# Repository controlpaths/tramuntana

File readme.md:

# Tramuntana — hardware hacking tool for embedded systems

An open bench tool for analysing and debugging embedded systems, built on
the RP2350 (Raspberry Pi Pico 2) and Zephyr OS. One USB cable, three serial
ports, one 16-pin header:

- **SPI master and sniffer** — SPIDriver-style `sel/write/read/unsel`
  transactions up to 75 MHz; passive full-duplex (MOSI + MISO) bus tap.
- **I2C master and sniffer** — I2CDriver-style `start/write/read/stop`
  primitives, scan, register access, bus recovery; passive decoder.
- **Oscilloscope** — 2 × 12-bit channels, 500 kS/s, pre-trigger.
- **Waveform generator** — sine/tri/saw/square/stairs/DC/arbitrary, 1 Hz–100 kHz.
- **Logic analyzer** — 8 channels, 150 MS/s, edge triggers in hardware,
  pattern trigger with pre-trigger, VCD export for PulseView.
- **USB-UART bridge** — the target's console as `/dev/ttyACM2`, baud rate
  follows whatever you open it with; RTS/DTR can drive the target's reset
  and boot pins, so esptool and friends flash through it.
- **Emulated I2C/SPI device** — the board answers on the target's bus from
  a register file the host loads and reads back.
- **Sequencer** — host-built step lists (GPIO, waits, bus transfers,
  captures) run on the board with microsecond timing.
- **Timeline** — the target's UART, sniffed buses, DIO edges and emulator
  transfers timestamped on one clock (host library, CLI, AI tools).
- Switched, protected 3.3 V rail for the target, switchable I2C pull-ups,
  RGB status LED and a TFT dashboard.

The passive instruments (sniffers, logic analyzer) only listen, so they can
watch a bus while the board's own master, the UART bridge or a target
drives it.

Two boards share the design: `tramuntana_r1a` (RP2350 on the PCB) and
`tramuntana_lite_r1a` (a Pico 2 soldered onto a two-layer carrier — the one
handed out at workshops). Firmware and host software are common.

## Documentation

The full documentation is in [`docs/`](docs/README.md): getting started,
a usage guide for every instrument, and complete references for the
Python library, the CLI, the shell, the binary protocol, the firmware
internals, the webapp and the AI tools.

## What's new

### Firmware 1.3.0, host package 2.3.0

Fixes found using the Tramuntana as the test bench of an FPGA module
library.

**Firmware**

- SPI emulator: written bytes go into the response table as they arrive,
  and the CS-rise interrupt rearms the shifters first. From CS rise to
  ready now takes under 2 µs; before, it took up to 160 µs after a
  write, and the next transaction was lost or garbled. A window that
  still starts too early is counted (`late`) and its event flagged
  `suspect`.
- I2C emulator: the START and STOP flags are read in one go. A STOP and
  the next START landing between two separate reads made the emulator
  NAK its own address after a write.
- I2C emulator: SDA is held ~330 ns after SCL falls (UM10204); it was
  30–140 ns.
- I2C sniffer: SCL must still be high a moment later before an SDA
  change counts as a START/STOP, so a slave with a short SDA hold no
  longer produces spurious STARTs or STOPs.
- Emulator events: the queue grows from 16 to 64, dropped events are
  counted and the next one is flagged (`gap`), reads log what went out
  on the bus, and display refreshes are rate-limited.
- Protocol: `EMU_STATUS` gains `dropped` and `late`; `EVT_EMU` flags
  bit 4 = suspect, bit 5 = gap.
- Sequencer: `PWM` (0x16) and `PWM_SYNC` (0x17) ops.

**Host**

- MCP server: `pwm_set` / `pwm_phase` / `pwm_sync` / `pwm_stop` /
  `pwm_status` tools, `pwm` ops in `sequence_run`, `spi_release` and
  `spi_transaction(release=)`, `names` as `{dio: name}`, and
  `logic_capture` waits up to 1 h (re-arming every 60 s).
- Library and CLI: `Spi.release()`, `tramuntana spi release`,
  `Sequence.pwm()` / `pwm_sync()`.
- Decoders: `sck_hz` / `scl_hz` are the median clock, and the new
  `bit_rate_hz` gives the average including pauses.
- `EmuTransfer.suspect` / `gap` and `Emu.status()` `dropped` / `late`;
  the webapp shows them.

**Docs:** measured SPI emulator speed limits, SPI master timing,
releasing pins after use, best-effort emulator events; the AI skill is
updated.

## Repository

```
fw/apps/tramuntana_fw/   Zephyr firmware                                -> its README
fw/boards/               devicetree for the board
fw/imgs/                 display images + font, with their generators
fw/build.sh              build / flash wrapper (local paths in fw/.env)
host/python/             Python package: library, `tramuntana` CLI, MCP server
                         and skill for AI agents                         -> its README
host/webapp/             browser front-end (Web Serial, no install)     -> its README
hw/tramuntana_lite_r1a/  KiCad project, hardware notes, 3D-printed case
hw/tramuntana_r1a/       KiCad project of the full board
docs/                    documentation                           -> its README
```

## Quick start

1. Flash `zephyr.uf2` from the latest GitHub release (hold BOOTSEL while
   plugging the Pico 2 in, copy the file to the `RP2350` drive), or build it
   yourself — see below. Three ports appear: shell, API, UART bridge.
2. Talk to it:

```bash
picocom /dev/ttyACM0           # the shell: try 'help', 'i2c scan', 'scope 1024'
source host/python/env.sh      # `tramuntana` command for this shell (creates the venv once)
tramuntana info
tramuntana i2c scan
tramuntana scope -n 2048 --trigger rising --level 1.65 --plot
tramuntana logic -n 65536 --rate 25M --vcd capture.vcd
picocom -b 115200 /dev/ttyACM2 # the target's UART, through the bridge
```

or open `host/webapp/index.html` in Chrome/Edge and press **Connect**.

3. Or hand it to an AI agent. The package carries an MCP server and the
   `tramuntana-debug` skill; one command registers both:

```bash
python3 -m venv ~/.venvs/tramuntana
~/.venvs/tramuntana/bin/pip install "./host/python[mcp]"
~/.venvs/tramuntana/bin/tramuntana ai install claude     # or opencode, copilot, all
# --project PATH registers it for that project only; 'ai uninstall' undoes it
```

Then ask: *"Power the target, scan the I2C bus and tell me what the devices
are."* See [AI tools](docs/19-ai-tools.md).

## `tramuntana` command reference

`source host/python/env.sh` defines the command in the current shell (it
runs `host/python/.venv/bin/tramuntana`, creating the venv the first time).
It talks to the board's API port, found automatically by USB id.

Conventions: bytes and I2C addresses are **hex** (`9f 00 ff`, `9f00ff`,
`68`); frequencies accept `k`/`M` suffixes (`400k`, `8M`, `1e6`); volts are
decimal (`1.65`). Exit code 0 on success, 1 if no board is found, 2 if the
board rejected the command (NAK, busy, bad argument…), 3 on a link error.

### Global options

| Option | Meaning |
|---|---|
| `--port /dev/ttyACMx` | use this API port instead of autodetecting |
| `--serial <id>` | pick the board with this USB serial number (several boards plugged in) |

### Board

| Command | What it does |
|---|---|
| `tramuntana list` | list connected boards and their shell / API / UART ports |
| `tramuntana info` | firmware version, board, system clock, chip id, protocol version, port |
| `tramuntana status` | who owns each DIO pin, power, pull-ups, state of every instrument, API bytes dropped |
| `tramuntana power [on\|off]` | switch the target's 3.3 V rail (J1.1); no argument prints its state |
| `tramuntana pullups [on\|off]` | I2C pull-up bias on DIO6/DIO7; no argument prints its state |
| `tramuntana led <colour>` | `off red green blue yellow cyan magenta white`, or `auto` to give it back to the firmware |
| `tramuntana adc [0\|1]` | one reading of AIN0/AIN1 in volts (default AIN0) |
| `tramuntana display <text…>` | show up to 24 characters on the board's screen |
| `tramuntana pinout [off] [--seconds N\|--hold]` | draw J1 (every pin's name and function) in the terminal and on the board's screen, 60 s by default; works without a board (terminal only) |
| `tramuntana dio read` | levels of DIO7..DIO0 |
| `tramuntana dio dir <mask> <out_mask>` | set direction of the pins in `mask` (bit i = DIOi, 1 = output) |
| `tramuntana dio write <mask> <value>` | drive the output pins in `mask` (set them as outputs first) |
| `tramuntana bootloader` | reboot into the UF2 bootloader (the `RP2350` drive appears) |

`dio` masks accept `0x..`, `0b..` or decimal (`0x0f`, `0b1010`, `15`).

### SPI — DIO2 CS, DIO3 MISO, DIO4 MOSI, DIO5 SCK

| Command | What it does |
|---|---|
| `tramuntana spi conf <freq> [mode] [--lsb]` | clock (up to 75 MHz), mode 0–3 (default 0), LSB first; prints the actual clock |
| `tramuntana spi sel` | CS low |
| `tramuntana spi unsel` | CS high |
| `tramuntana spi release` | stop driving DIO2..5 (the master leaves CS, SCK and MOSI driven after each command) |
| `tramuntana spi write <bytes…>` | send bytes, CS untouched |
| `tramuntana spi read <n>` | read n bytes (sends 0x00), CS untouched |
| `tramuntana spi xfer <bytes…>` | full duplex: send bytes, print what came back, CS untouched |
| `tramuntana spi txn [bytes…] [--read N]` | whole transaction: CS low, write bytes, read N, CS high |
| `tramuntana spi sniff [--mode M]` | passive tap of MOSI and MISO, one line per CS-low message, until Ctrl-C (mode defaults to the one set with `conf`) |

```bash
tramuntana spi conf 8M 0
tramuntana spi txn 9f --read 3                  # JEDEC id of a SPI flash
tramuntana spi txn 03 00 00 00 --read 256       # first page of the flash
tramuntana spi sel && tramuntana spi write 06 && tramuntana spi unsel   # write enable, step by step
```

### I2C — DIO6 SCL, DIO7 SDA

| Command | What it does |
|---|---|
| `tramuntana i2c conf <freq> [--no-pullups]` | bus clock (1 kHz–1 MHz); turns the board's pull-ups on unless `--no-pullups` |
| `tramuntana i2c scan` | probe 0x08–0x77 and print the address map |
| `tramuntana i2c read <addr>` | read 1 byte from a device |
| `tramuntana i2c read <addr> <reg> [n]` | register read: write `reg`, repeated START, read n bytes (default 1). `reg` takes 2 hex digits per byte, so `0010` is a 16-bit address (24LC32 and up, VL53L1X…) |
| `tramuntana i2c write <addr> <bytes…>` | START, address, bytes, STOP; prints how many bytes were ACKed |
| `tramuntana i2c regs <addr>` | dump registers 0x00–0xff (16 at a time; blocks that NAK show as `ff`) |
| `tramuntana i2c sniff [--pullups]` | passive decoder, one line per START…STOP (`S 68W+ 75+  S 68R+ 71- P`), until Ctrl-C |
| `tramuntana i2c reset` | bus recovery: up to 9 SCL pulses and a STOP to free a stuck slave |

```bash
tramuntana i2c conf 400k
tramuntana i2c scan
tramuntana i2c read 68 75              # WHO_AM_I of an MPU-6050
tramuntana i2c write 68 6b 00          # wake it up
tramuntana i2c regs 50                 # dump an EEPROM's first 256 bytes
```

The low-level primitives (`start`, raw write/read, `stop`) are in the shell,
the Python library and the webapp; the CLI covers complete transactions.

### Oscilloscope — AIN0 (and AIN1)

`tramuntana scope [options]` captures, prints per-channel min / max / Vpp /
mean / RMS / frequency, and optionally saves or plots.

| Option | Default | Meaning |
|---|---|---|
| `-n N` | 2048 | samples per channel (16384 in total max) |
| `--ch 1\|2` | 1 | AIN0 only, or AIN0 + AIN1 |
| `--rate R` | 500k | sample rate per channel (500 kS/s total max, shared between channels) |
| `--trigger none\|rising\|falling` | none | edge on AIN0 |
| `--level V` | 1.65 | trigger level in volts |
| `--pre N` | 0 | samples kept before the trigger |
| `--csv file` | | save `t,ch0[,ch1]` in volts, t = 0 at the trigger |
| `--plot` | | show it with matplotlib (`host/python/.venv/bin/pip install matplotlib`) |

```bash
tramuntana scope -n 4096 --trigger rising --level 1.65 --pre 1024 --plot
tramuntana scope --ch 2 --rate 100k --csv two_channels.csv
```

### Waveform generator — AOUT0

| Command | What it does |
|---|---|
| `tramuntana awg sine <freq> [--amp V] [--offset V]` | sine; amplitude is the peak around the offset (defaults 1.0 V around 1.65 V) |
| `tramuntana awg tri <freq> [--amp V] [--offset V]` | triangle |
| `tramuntana awg saw <freq> [--amp V] [--offset V]` | sawtooth (rising ramp) |
| `tramuntana awg square <freq> [--amp V] [--offset V] [--param duty%]` | square, duty cycle in % (default 50) |
| `tramuntana awg stairs <freq> [--amp V] [--offset V] [--param steps]` | staircase with that many steps (default 8) |
| `tramuntana awg dc <volts>` | constant level |
| `tramuntana awg step <from_v> <to_v> <ms>` | hold `from_v`, then jump to `to_v` after `ms` |
| `tramuntana awg off` | stop, output low |
| `tramuntana awg status` | what is running |

Frequencies go from 1 Hz to 100 kHz; the command prints the frequency
actually achieved. Arbitrary waveforms are loaded from the Python library
(`t.awg.arbitrary(...)`) or the webapp.

### PWM outputs — any DIO

| Command | What it does |
|---|---|
| `tramuntana pwm set <dio> <freq> <duty%> [--invert]` | PWM on a DIO; pairs 7/6, 5/4, 3/2, 1/0 share a frequency |
| `tramuntana pwm phase <dio> <deg>` / `pwm sync [mask]` | phase per pair, restart the pairs together |
| `tramuntana pwm stop <dio\|all>` / `pwm status` | stop / show every output |

### Logic analyzer — DIO0..DIO7

`tramuntana logic [options]` captures, prints the number of transitions per
channel, and optionally saves or plots.

| Option | Default | Meaning |
|---|---|---|
| `-n N` | 16384 | samples (131072 max, 122880 with a pattern trigger) |
| `--rate R` | 150M | sample rate (150 MS/s max; 15 MS/s max with a pattern trigger) |
| `--trigger none\|rising\|falling\|pattern` | none | edge on one pin, or a pattern on several |
| `--pin P` | 0 | DIO used by `rising`/`falling` |
| `--mask M` / `--value V` | 0 / 0 | pattern trigger: fires when `(sample & mask) == value` (bit i = DIOi) |
| `--pre N` | 0 | samples kept before the trigger (pattern trigger only) |
| `--timeout ms` | 5000 | give up if the trigger doesn't come |
| `--vcd file` | | save for PulseView / GTKWave |
| `--csv file` | | save `t,DIO0..DIO7`, t = 0 at the trigger |
| `--plot` | | show the 8 lanes with matplotlib |

```bash
tramuntana logic -n 131072 --rate 150M --trigger rising --pin 5 --vcd spi.vcd
tramuntana logic -n 100000 --rate 10M --trigger pattern --mask 0x80 --value 0 --pre 2000 --vcd i2c.vcd   # I2C START (SDA low)
```

### UART bridge — DIO1 TX, DIO0 RX

| Command | What it does |
|---|---|
| `tramuntana uart` / `tramuntana uart status` | bridge active or not, baud rate, bytes received / sent, and which port to open |
| `tramuntana uart auto` | (default) bridge on while a program has the bridge port open |
| `tramuntana uart on [--baud B]` | force it on; `--baud` overrides the rate the host sets on the port |
| `tramuntana uart off` | force it off, DIO0/DIO1 free for plain GPIO |

The data itself goes through the third serial port, e.g.
`picocom -b 115200 /dev/ttyACM2` (the baud rate you open it with is the one
used on the target, unless overridden with `--baud`).

| Command | What it does |
|---|---|
| `tramuntana uart ctrl esp --reset R --boot B` | RTS/DTR of the bridge port drive DIO R / DIO B (open-drain) with the ESP32/ESP8266 auto-reset logic: `esptool --port /dev/ttyACM2 ...` resets the target into its ROM loader by itself |
| `tramuntana uart ctrl direct --reset R --boot B` | reset follows RTS, boot follows DTR (an adapter wired straight to the pins) |
| `tramuntana uart ctrl off` | release them |

### Emulated device, timeline, DIO watch

| Command | What it does |
|---|---|
| `tramuntana emu i2c ADDR [--scl D --sda D] [--pullups] [--set REG=HEX..]` | answer as an I2C device at ADDR (default on DIO6/DIO7), registers loaded first |
| `tramuntana emu spi [--mode M] [--cs --sck --mosi --miso D] [--set REG=HEX..]` | answer as a SPI device (bit 7 of the command byte = read) |
| `tramuntana emu set REG HEX..` / `emu regs [REG] [N]` | load / dump registers |
| `tramuntana emu status` / `emu log` / `emu off` | counters / live transfers / stop |
| `tramuntana watch MASK` | timestamped edges on the DIOs in MASK, until Ctrl-C |
| `tramuntana timeline [--watch MASK] [--uart BAUD] [--i2c] [--spi MODE]` | live timeline: the target's UART lines, sniffed messages, DIO edges and emulator transfers on one clock |

The sequencer has no CLI front: build a `Sequence` in Python
([API](host/python/API.md#tseq--sequencer)) or use the AI tools'
`sequence_run`.

## Building the firmware

A Zephyr workspace (per the
[getting started guide](https://docs.zephyrproject.org/latest/develop/getting_started/index.html))
and the Zephyr SDK, plus `device-tree-compiler` on the host. `fw/` is not
its own west workspace; `build.sh` builds an app against that install.
Tell it where they are in `fw/.env` (defaults: `~/zephyrproject` and
`~/zephyr-sdk-1.0.1`):

```bash
cd fw
cp .env.example .env             # then edit ZEPHYRPROJECT / ZEPHYR_SDK
./build.sh                       # builds tramuntana_fw
./build.sh flash                 # build + flash (reboots the board into the
                                 # UF2 bootloader over USB, no BOOTSEL needed)
```

Only the first flash — or recovering from a hung firmware — needs BOOTSEL
held while plugging the board in.

## Header

```
 1 3V3 (switched)   2 GND       3 AIN0     4 GND      5 AIN1    6 GND
 7 AOUT0            8 VREF      9 DIO0    10 DIO1    11 DIO2   12 DIO3
13 DIO4            14 DIO5     15 DIO6    16 DIO7

DIO0/1 = UART RX/TX    DIO2..5 = SPI CS / MISO / MOSI / SCK    DIO6/7 = I2C SCL/SDA
DIO0..7 = GPIO and logic analyzer channels 0..7   (`tramuntana pinout` draws it)
```

## License

| Part | License |
|---|---|
| Firmware (`fw/`), host software (`host/`: library, CLI, MCP server, webapp) | [MIT](LICENSES/MIT.txt) |
| Hardware (`hw/`: schematics, PCB, fabrication files, case) | [CERN-OHL-P-2.0](LICENSES/CERN-OHL-P-2.0.txt) |
| Documentation (`docs/`, READMEs, images) | [CC-BY-4.0](LICENSES/CC-BY-4.0.txt) |

See [LICENSE](LICENSE).

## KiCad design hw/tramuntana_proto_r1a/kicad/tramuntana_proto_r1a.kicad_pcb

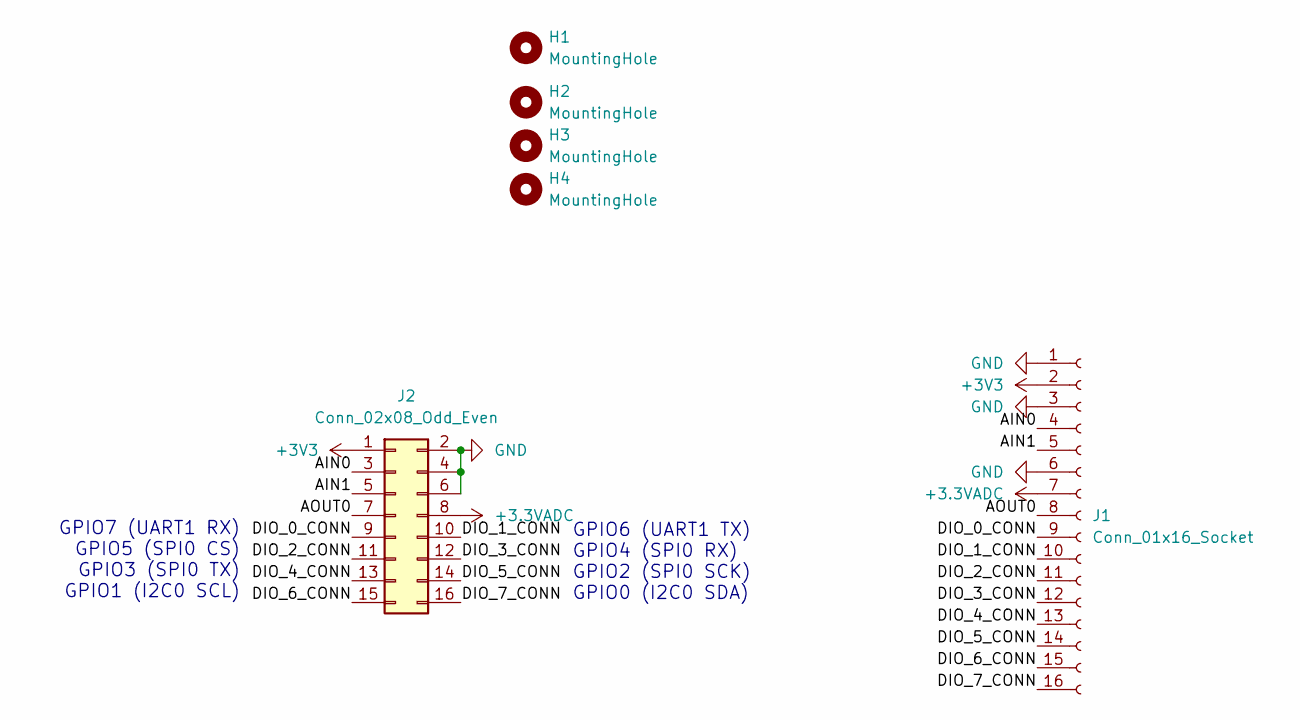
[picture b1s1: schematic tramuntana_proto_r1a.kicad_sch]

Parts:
H1, H2, H3, H4: MountingHole; MountingHole_3.2mm_M3
J1: Conn_01x16_Socket; PinSocket_1x16_P2.54mm_Vertical
J2: Conn_02x08_Odd_Even; PinSocket_2x08_P2.54mm_Horizontal

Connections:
+3.3VADC: J1.7, J2.8
+3V3: J1.2, J2.1
/AIN0: J1.4, J2.3
/AIN1: J1.5, J2.5
/AOUT0: J1.8, J2.7
/DIO_0_CONN: J1.9, J2.9
/DIO_1_CONN: J1.10, J2.10
/DIO_2_CONN: J1.11, J2.11
/DIO_3_CONN: J1.12, J2.12
/DIO_4_CONN: J1.13, J2.13
/DIO_5_CONN: J1.14, J2.14
/DIO_6_CONN: J1.15, J2.15
/DIO_7_CONN: J1.16, J2.16
GND: J1.1, J1.3, J1.6, J2.2, J2.4, J2.6

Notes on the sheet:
GPIO7 (UART1 RX) GPIO5 (SPI0 CS) GPIO3 (SPI0 TX) GPIO1 (I2C0 SCL)
GPIO6 (UART1 TX) GPIO4 (SPI0 RX) GPIO2 (SPI0 SCK) GPIO0 (I2C0 SDA)

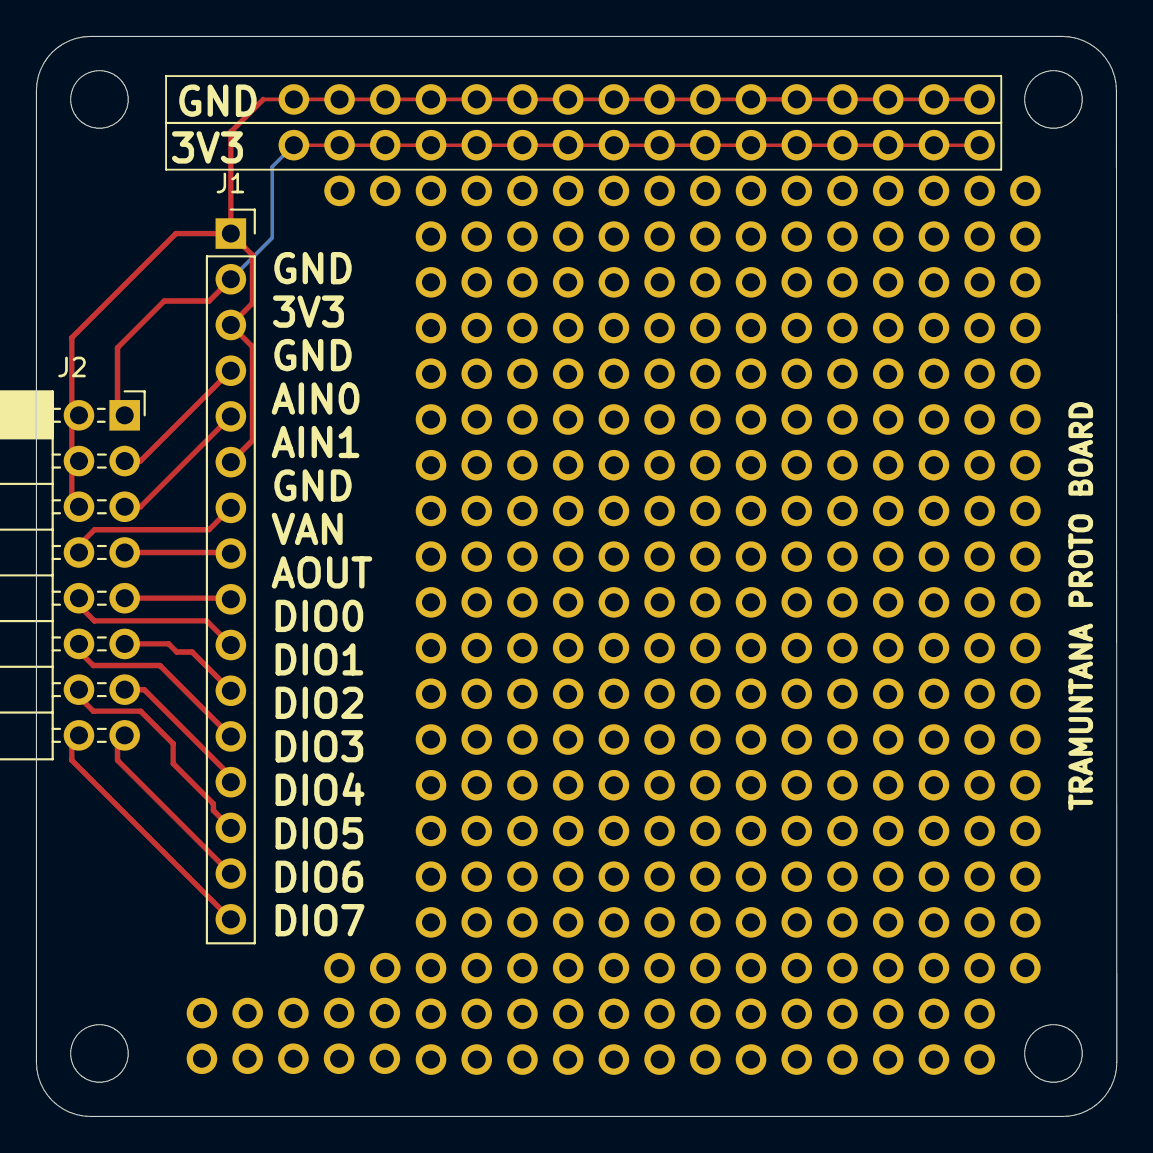
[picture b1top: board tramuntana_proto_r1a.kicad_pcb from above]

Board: 2 copper layers, 60.0 x 60.0 mm, 6 parts (0 on the bottom side), 14 nets.

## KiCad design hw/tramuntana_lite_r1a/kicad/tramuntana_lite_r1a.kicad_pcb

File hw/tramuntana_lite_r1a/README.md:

# Tramuntana Lite r1a

RP2350-based board. The KiCad project lives in [kicad/](kicad/). Firmware
for this board lives in the workspace-wide [../../fw/](../../fw/) tree (see
its README for building/flashing) — bring-up is happening on a
**Raspberry Pi Pico 2** (RP2350) ahead of the final board, since the MCU
(A1 in the schematic) is a Pico module soldered straight onto this board.

---

## Board devicetree

There's no dedicated Zephyr board port for tramuntana_lite_r1a (that's more
machinery than a bring-up needs). Instead, the hardware is described in
[../../fw/boards/tramuntana_lite_r1a-common.dtsi](../../fw/boards/tramuntana_lite_r1a-common.dtsi) —
an app-level devicetree overlay applied on top of the stock
`rpi_pico2/rp2350a/m33` board, shared by every app under `fw/apps/`.

### What's on the board

Derived from the schematic netlist ([kicad/tramuntana_lite_r1a.kicad_sch](kicad/tramuntana_lite_r1a.kicad_sch),
cross-checked against `kicad-cli sch export netlist`):

| Header pin | Net | Pico GPIO | Devicetree |
|---|---|---|---|
| J1.1 | `/3V3_TARGET` (switched, via Q1) | GPIO11 (enable, active-low) | `regulator-fixed`, alias `targetpwr` |
| J1.3 | `/AIN0` | GPIO26 / ADC0 | `&adc`, channel 0 |
| J1.5 | `/AIN1` | GPIO27 / ADC1 | `&adc`, channel 1 |
| J1.7 | `/AOUT0` | GPIO8 | `zephyr,user` / `aout0-gpios` |
| J1.9-16 | `DIO0`..`DIO7` | GPIO7..GPIO0 | `zephyr,user` / `dio-gpios` |
| — | `/DIO_PU_ENABLE` (shared pull-up bias for DIO6/DIO7) | GPIO10 | `zephyr,user` / `dio-pu-enable-gpios` |
| J1.11-14 (DIO2-5) | SPI0 CSN/RX/TX/SCK | GPIO5/4/3/2 | `&spi0` (hardware CS on DIO2) |
| J1.15-16 (DIO6/7) | I2C0 SCL/SDA | GPIO1/0 | `&i2c0` (100kHz by default) |
| J2.3/4 | SPI1 SCK/MOSI | GPIO14/15 | `&spi1` (hardware CS on GPIO13) |
| J2.5/6/7 | TFT reset/DC/CS | GPIO16/17/13 | the `zephyr,mipi-dbi-spi` + `sitronix,st7735r` nodes |
| D3 (RGB LED) | `/LEDR`, `/LEDG`, `/LEDB` | GPIO20/21/22 | `gpio-leds` (active-low), aliases `led-r`/`led-g`/`led-b` |

Q1 is a P-FET high-side switch (R17 pulls its gate to +3V3 at reset, so the
rail is off by default); D3 is a common-anode RGB LED, so all three legs
sink current through their GPIO and are active-low. D7 (power-good LED) and
the protection parts (F1 fuse, D1/D2 clamps, the series resistors) aren't
modeled — they're not GPIO-controlled, just electrical protection and
indication.

Confirmed on real hardware: D3's red and green legs are swapped relative to
the schematic's own net names (`LEDR`/`LEDG`) — GPIO20 is actually green and
GPIO21 is actually red, the opposite of what the net names say. The
devicetree's `led-r`/`led-g` aliases are wired to match reality (GPIO21/
GPIO20), not the schematic labels, so software colors are correct even
though the underlying net names are misleading.

One thing worth knowing: UART0 (GPIO0/GPIO1) is this board target's default
Zephyr console, and that's DIO7/DIO6 on the target header here — the same
two pins `&i2c0` uses. The firmware (`tramuntana_fw`) overrides the
console to run over the Pico's own USB port (CDC-ACM) instead, precisely to
keep those two header pins free for I2C. Any other app built for this board
that doesn't override it still uses UART0 for its boot log — keep J1's DIO6/DIO7
unplugged while flashing/testing those, and don't expect I2C0 to work in
them at the same time as the console.

`&spi0` and `&i2c0` are enabled alongside `dio-gpios`'s plain-GPIO view of
the same pins (DIO2-7): nothing stops an app from referencing both, but the
RP2350 only drives one function per pin at a time, so pick whichever one an
app actually needs for DIO2-7 rather than mixing them on the same pins.

The display node assumes a generic 1.8" 128x160 ST7735R module (GND, 3V3,
SCK, MOSI, RST, DC, CS, BL on J2, in that order; BL is tied straight to
+3V3, no GPIO control). If the picture comes out shifted or mirrored, that's
the well-known ST7735 clone quirk where `x-offset`/`y-offset`/`madctl` differ
by tab color — adjust them in `tramuntana_lite_r1a-common.dtsi`.

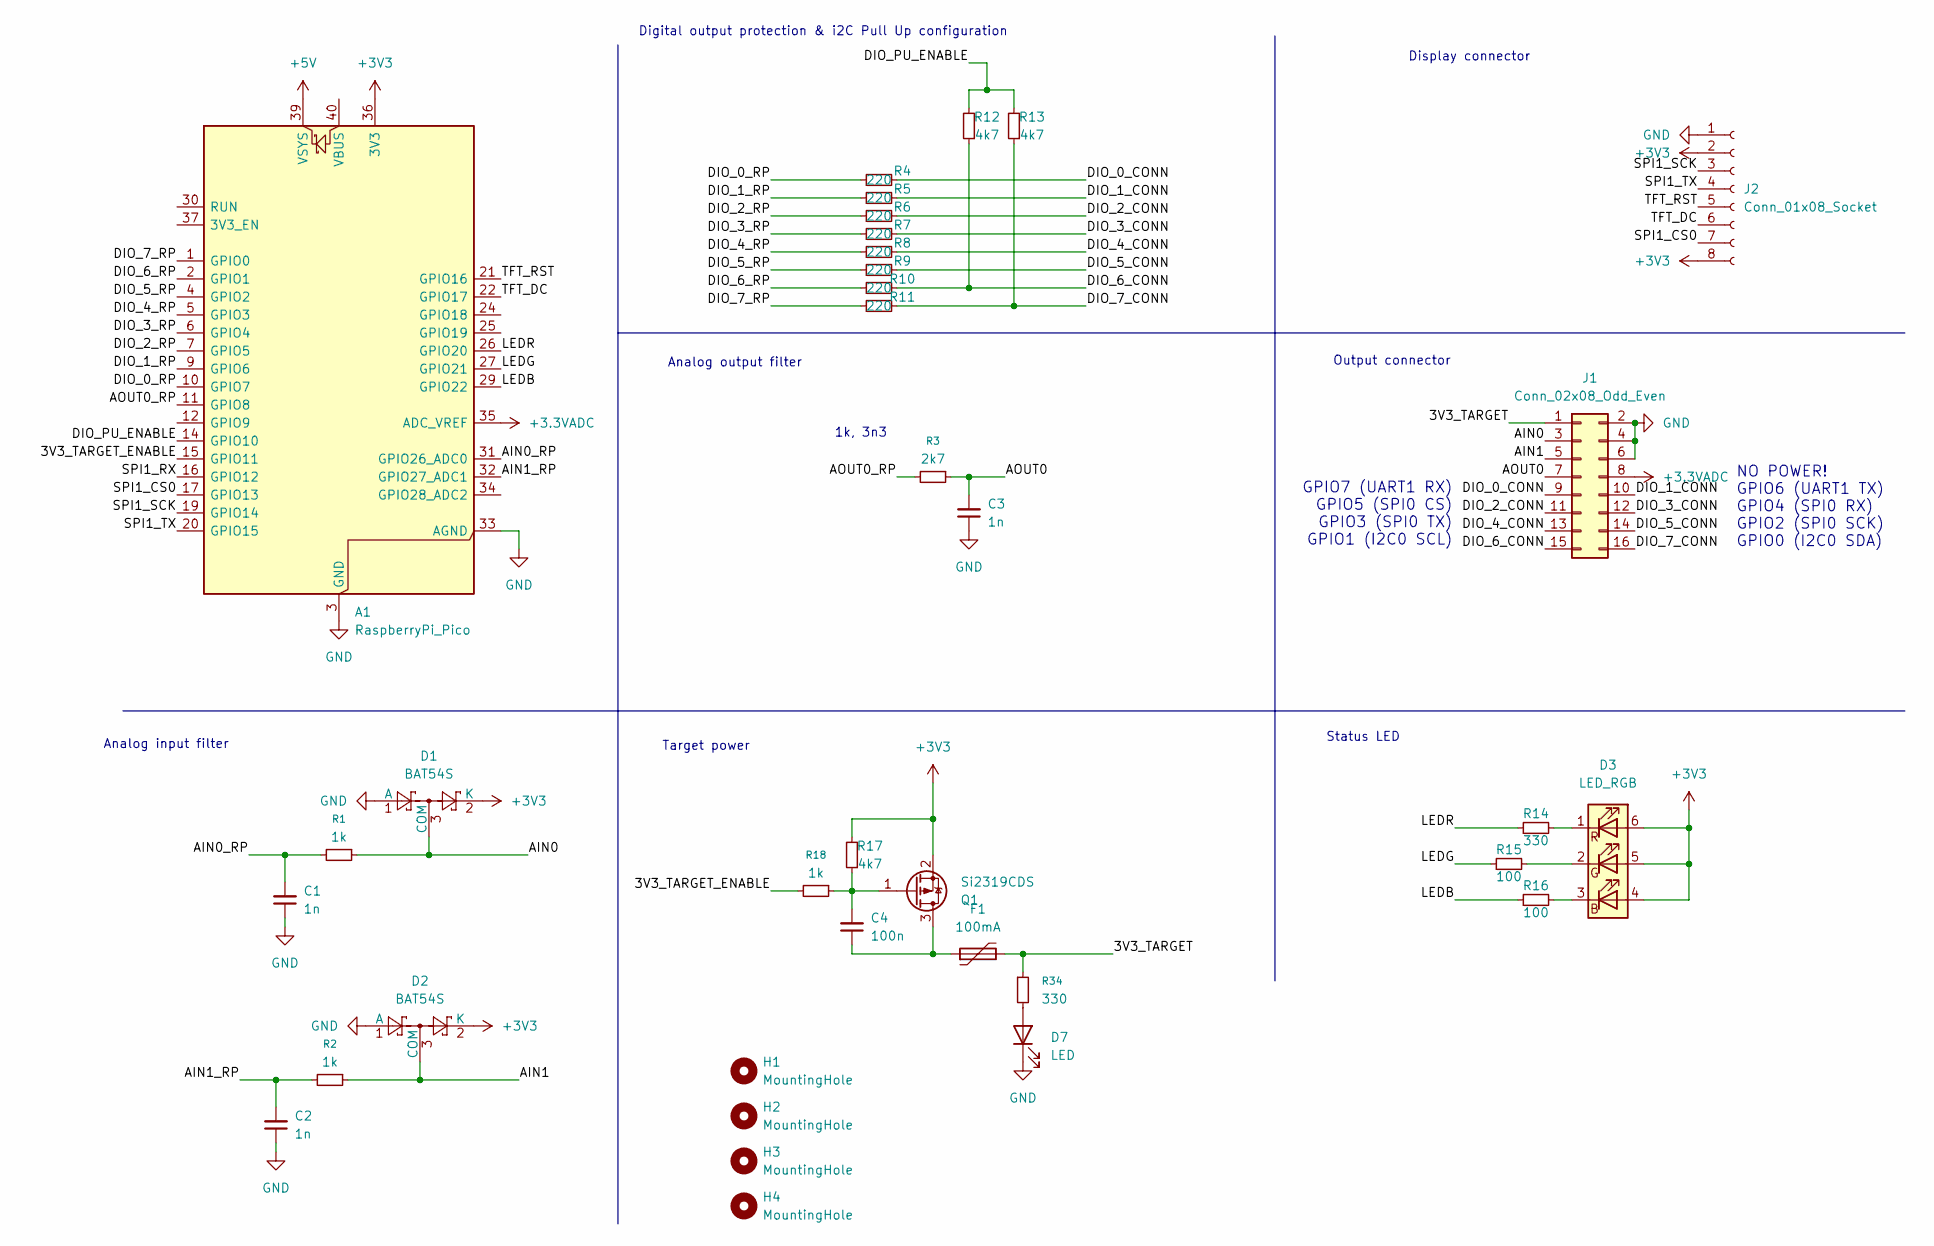
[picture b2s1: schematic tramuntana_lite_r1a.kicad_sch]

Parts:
A1: RaspberryPi_Pico; RaspberryPi_Pico_Common_Unspecified
C1, C2, C3: 1n; C_0603_1608Metric_Pad1.08x0.95mm_HandSolder
C4: 100n; C_0603_1608Metric_Pad1.08x0.95mm_HandSolder
D1, D2: BAT54S; SOT-23
D3: LED_RGB; LED_RGB_5050-6
D7: LED; LED_0603_1608Metric
F1: 100mA; Fuse_0805_2012Metric
H1, H2, H3, H4: MountingHole; MountingHole_3.2mm_M3
J1: Conn_02x08_Odd_Even; PinHeader_2x08_P2.54mm_Horizontal
J2: Conn_01x08_Socket; PinHeader_1x08_P2.54mm_Vertical
Q1: Si2319CDS; SOT-23
R1, R2: 1k; R_0603_1608Metric_Pad0.98x0.95mm_HandSolder
R3: 2k7; R_0603_1608Metric_Pad0.98x0.95mm_HandSolder
R4, R5, R6, R7, R8, R9, R10, R11: 220; R_0603_1608Metric
R12, R13, R17: 4k7; R_0603_1608Metric
R14: 330; R_0603_1608Metric
R15, R16: 100; R_0603_1608Metric
R18: 1k; R_0603_1608Metric
R34: 330; R_0603_1608Metric_Pad0.98x0.95mm_HandSolder

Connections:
+3.3VADC: A1.35 (ADC_VREF), J1.8
+3V3: A1.36 (3V3), D1.2 (K), D2.2 (K), D3.4 (BA), D3.5 (GA), D3.6 (RA), J2.2, J2.8, Q1.2 (S), R17.2
+5V: A1.39 (VSYS)
/3V3_TARGET: F1.2, J1.1, R34.1
/3V3_TARGET_ENABLE: A1.15 (GPIO11), R18.2
/AIN0: D1.3 (COM), J1.3, R1.1
/AIN0_RP: A1.31 (GPIO26_ADC0), C1.2, R1.2
/AIN1: D2.3 (COM), J1.5, R2.1
/AIN1_RP: A1.32 (GPIO27_ADC1), C2.2, R2.2
/AOUT0: C3.2, J1.7, R3.1
/AOUT0_RP: A1.11 (GPIO8), R3.2
/DIO_0_CONN: J1.9, R4.2
/DIO_0_RP: A1.10 (GPIO7), R4.1
/DIO_1_CONN: J1.10, R5.2
/DIO_1_RP: A1.9 (GPIO6), R5.1
/DIO_2_CONN: J1.11, R6.2
/DIO_2_RP: A1.7 (GPIO5), R6.1
/DIO_3_CONN: J1.12, R7.2
/DIO_3_RP: A1.6 (GPIO4), R7.1
/DIO_4_CONN: J1.13, R8.2
/DIO_4_RP: A1.5 (GPIO3), R8.1
/DIO_5_CONN: J1.14, R9.2
/DIO_5_RP: A1.4 (GPIO2), R9.1
/DIO_6_CONN: J1.15, R10.2, R12.1
/DIO_6_RP: A1.2 (GPIO1), R10.1
/DIO_7_CONN: J1.16, R11.2, R13.1
/DIO_7_RP: A1.1 (GPIO0), R11.1
/DIO_PU_ENABLE: A1.14 (GPIO10), R12.2, R13.2
/LEDB: A1.29 (GPIO22), R16.1
/LEDG: A1.27 (GPIO21), R15.1
/LEDR: A1.26 (GPIO20), R14.1
/SPI1_CS0: A1.17 (GPIO13), J2.7
/SPI1_RX: A1.16 (GPIO12)
/SPI1_SCK: A1.19 (GPIO14), J2.3
/SPI1_TX: A1.20 (GPIO15), J2.4
/TFT_DC: A1.22 (GPIO17), J2.6
/TFT_RST: A1.21 (GPIO16), J2.5
GND: A1.3 (GND), A1.8 (GND), A1.13 (GND), A1.18 (GND), A1.23 (GND), A1.28 (GND), A1.33 (AGND), A1.38 (GND), C1.1, C2.1, C3.1, D1.1 (A), D2.1 (A), D7.1 (K), J1.2, J1.4, J1.6, J2.1
unnamed: D3.3 (BK), R16.2
unnamed: D3.2 (GK), R15.2
unnamed: D3.1 (RK), R14.2
unnamed: D7.2 (A), R34.2
unnamed: C4.1, F1.1, Q1.3 (D)
unnamed: C4.2, Q1.1 (G), R17.1, R18.1

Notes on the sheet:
Target power
Output connector
Analog output filter
Analog input filter
NO POWER! GPIO6 (UART1 TX) GPIO4 (SPI0 RX) GPIO2 (SPI0 SCK) GPIO0 (I2C0 SDA)
Display connector
Status LED
Digital output protection & i2C Pull Up configuration
1k, 3n3
GPIO7 (UART1 RX) GPIO5 (SPI0 CS) GPIO3 (SPI0 TX) GPIO1 (I2C0 SCL)

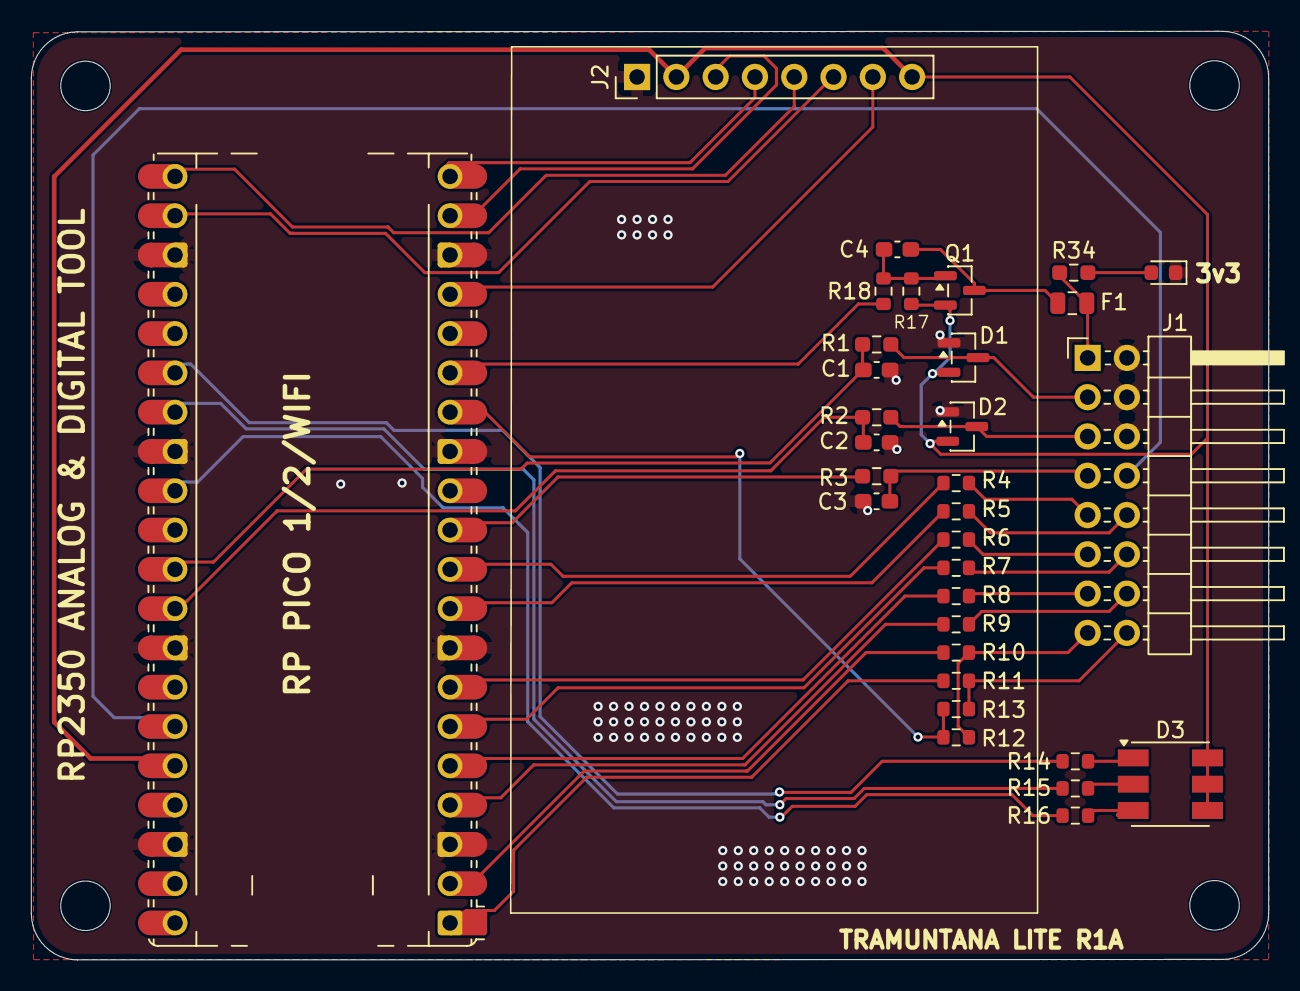
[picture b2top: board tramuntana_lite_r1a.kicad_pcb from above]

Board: 2 copper layers, 80.0 x 60.0 mm, 36 parts (0 on the bottom side), 42 nets.

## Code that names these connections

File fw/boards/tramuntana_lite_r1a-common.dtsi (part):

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 *
 *   Header pin | Net              | Pico GPIO | Devicetree
 *   -----------|------------------|-----------|---------------------------
 *   J1.1       | /3V3_TARGET      | GPIO11    | regulator-fixed, alias targetpwr
 *   J1.3       | /AIN0            | GPIO26    | &adc channel 0
 *   J1.5       | /AIN1            | GPIO27    | &adc channel 1
 *   J1.7       | /AOUT0           | GPIO8     | &pwm slice 4A (aout0_pwm_default)
 *   J1.9-16    | DIO0..DIO7       | GPIO7..0  | zephyr,user dio-gpios
 *   -          | /DIO_PU_ENABLE   | GPIO10    | zephyr,user dio-pu-enable-gpios
 *   J2.3/4     | SPI1 SCK/MOSI    | GPIO14/15 | &spi1
 *   J2.5/6/7   | TFT RST/DC/CS    | GPIO16/17/13 | mipi-dbi-spi + st7735r
 *   D3         | LEDR/LEDG/LEDB   | GPIO20/21/22 | gpio-leds, alias led-r/g/b
 *
 * DIO2..DIO5 (GPIO5..2) and DIO6/DIO7 (GPIO1/0) double as the RP2350's
 * native SPI0 and I2C0, since that's what the connector's 8 GPIOs are for:
 *
 *   DIO pin | Pico GPIO | SPI0 signal | I2C0 signal
 *   --------|-----------|-------------|------------
 *   DIO2    | GPIO5     | CSN         | -
 *   DIO3    | GPIO4     | RX (MISO)   | -
 *   DIO4    | GPIO3     | TX (MOSI)   | -
 *   DIO5    | GPIO2     | SCK         | -
 *   DIO6    | GPIO1     | -           | SCL
 *   DIO7    | GPIO0     | -           | SDA
 *
 * &spi0/&i2c0 below are enabled alongside dio-gpios's plain-GPIO view of
 * the same pins - nothing stops an app from using both nodes, but only one
 * function actually drives a given pin at a time, so pick one per DIO pin
 * in practice. DIO6/DIO7 (I2C0) also double as UART0 (GPIO0/1), Zephyr's
 * default console on this board target - see the note further down.
 * tramuntana_fw disables UART0 and runs its bridge on UART1 instead, at
 * DIO1 (GPIO6, TX) / DIO0 (GPIO7, RX) through the UART_AUX pin function.
 *
 * Series resistors, the target-rail fuse/clamp diodes and the power-good
 * LED (D7) are electrical protection/indication only - not modeled here.
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  };

  /* Q1 (P-FET high-side switch) gates the target's 3.3V rail. R17 pulls
   * the gate to 3V3 (off) at reset; GPIO11 low turns the rail on. */
  target_3v3_regulator: regulator-target-3v3 {
    compatible = "regulator-fixed";
    regulator-name = "target-3v3-regulator";
    enable-gpios = <&gpio0 11 GPIO_ACTIVE_LOW>;
    regulator-boot-off;
  };

  /* D3 is a common-anode RGB LED tied to +3V3: each leg sinks current
   * through the RP2350 GPIO, so all three lines are active-low.
   *
   * The schematic nets are named LEDR=GPIO20/LEDG=GPIO21/LEDB=GPIO22, but
   * on real hardware GPIO20 lights the green leg and GPIO21 the red one
   * (D3's symbol/footprint pinout doesn't match its net names) - swapped
   * here so led-r/led-g actually match what lights up. */
  leds {
    compatible = "gpio-leds";
    led_r: led-r {
      gpios = <&gpio0 21 GPIO_ACTIVE_LOW>;
    };
    led_g: led-g {
      gpios = <&gpio0 20 GPIO_ACTIVE_LOW>;
    };
    led_b: led-b {
      gpios = <&gpio0 22 GPIO_ACTIVE_LOW>;
    };
  };

  /* J1's 8 general-purpose header pins, exposed as plain GPIOs. DIO0..DIO7
   * map to GPIO7..GPIO0 (reversed on the header). aout0-gpios is kept for
   * reference only - GPIO8 is muxed to PWM by &pwm's pinctrl below, and
   * configuring it as a GPIO would undo that. */
  zephyr_user: zephyr,user {
    dio-gpios = <&gpio0 7 GPIO_ACTIVE_HIGH>, <&gpio0 6 GPIO_ACTIVE_HIGH>,
                <&gpio0 5 GPIO_ACTIVE_HIGH>, <&gpio0 4 GPIO_ACTIVE_HIGH>,
                <&gpio0 3 GPIO_ACTIVE_HIGH>, <&gpio0 2 GPIO_ACTIVE_HIGH>,
                <&gpio0 1 GPIO_ACTIVE_HIGH>, <&gpio0 0 GPIO_ACTIVE_HIGH>;
    aout0-gpios = <&gpio0 8 GPIO_ACTIVE_HIGH>;
    dio-pu-enable-gpios = <&gpio0 10 GPIO_ACTIVE_HIGH>;
    io-channels = <&adc 0>, <&adc 1>;
  };

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  mipi_dbi_lite: mipi-dbi-lite {
    compatible = "zephyr,mipi-dbi-spi";
    spi-dev = <&spi1>;
    dc-gpios = <&gpio0 17 GPIO_ACTIVE_HIGH>;
    reset-gpios = <&gpio0 16 GPIO_ACTIVE_LOW>;
    write-only;
    #address-cells = <1>;
    #size-cells = <0>;
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
  /* Named dio_* rather than the usual spi0_default/i2c0_default: those
   * labels already exist in the stock rpi_pico2 pinctrl file on different
   * pins (GPIO16-19 and GPIO4/5) - reusing them would silently override
   * that node instead of adding a new one. */
  dio_spi0_default: dio_spi0_default {
    group1 {
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    };
  };

  /* AOUT0 = GPIO8 = PWM slice 4 channel A, behind R3/C3 (2k7/1nF). */
  aout0_pwm_default: aout0_pwm_default {
    group1 {
      pinmux = <PWM_4A_P8>;
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
/* The 'aout' waveform generator (src/aout.c) drives slice 4 straight from
 * hardware/pwm.h; enabling the node here is what brings the PWM block out
 * of reset and muxes GPIO8 to it at boot. */
&pwm {
  pinctrl-0 = <&aout0_pwm_default>;
  pinctrl-names = "default";
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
